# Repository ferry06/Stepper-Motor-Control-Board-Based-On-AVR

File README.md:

# Stepper-Motor-Control-Board-Based-On-AVR

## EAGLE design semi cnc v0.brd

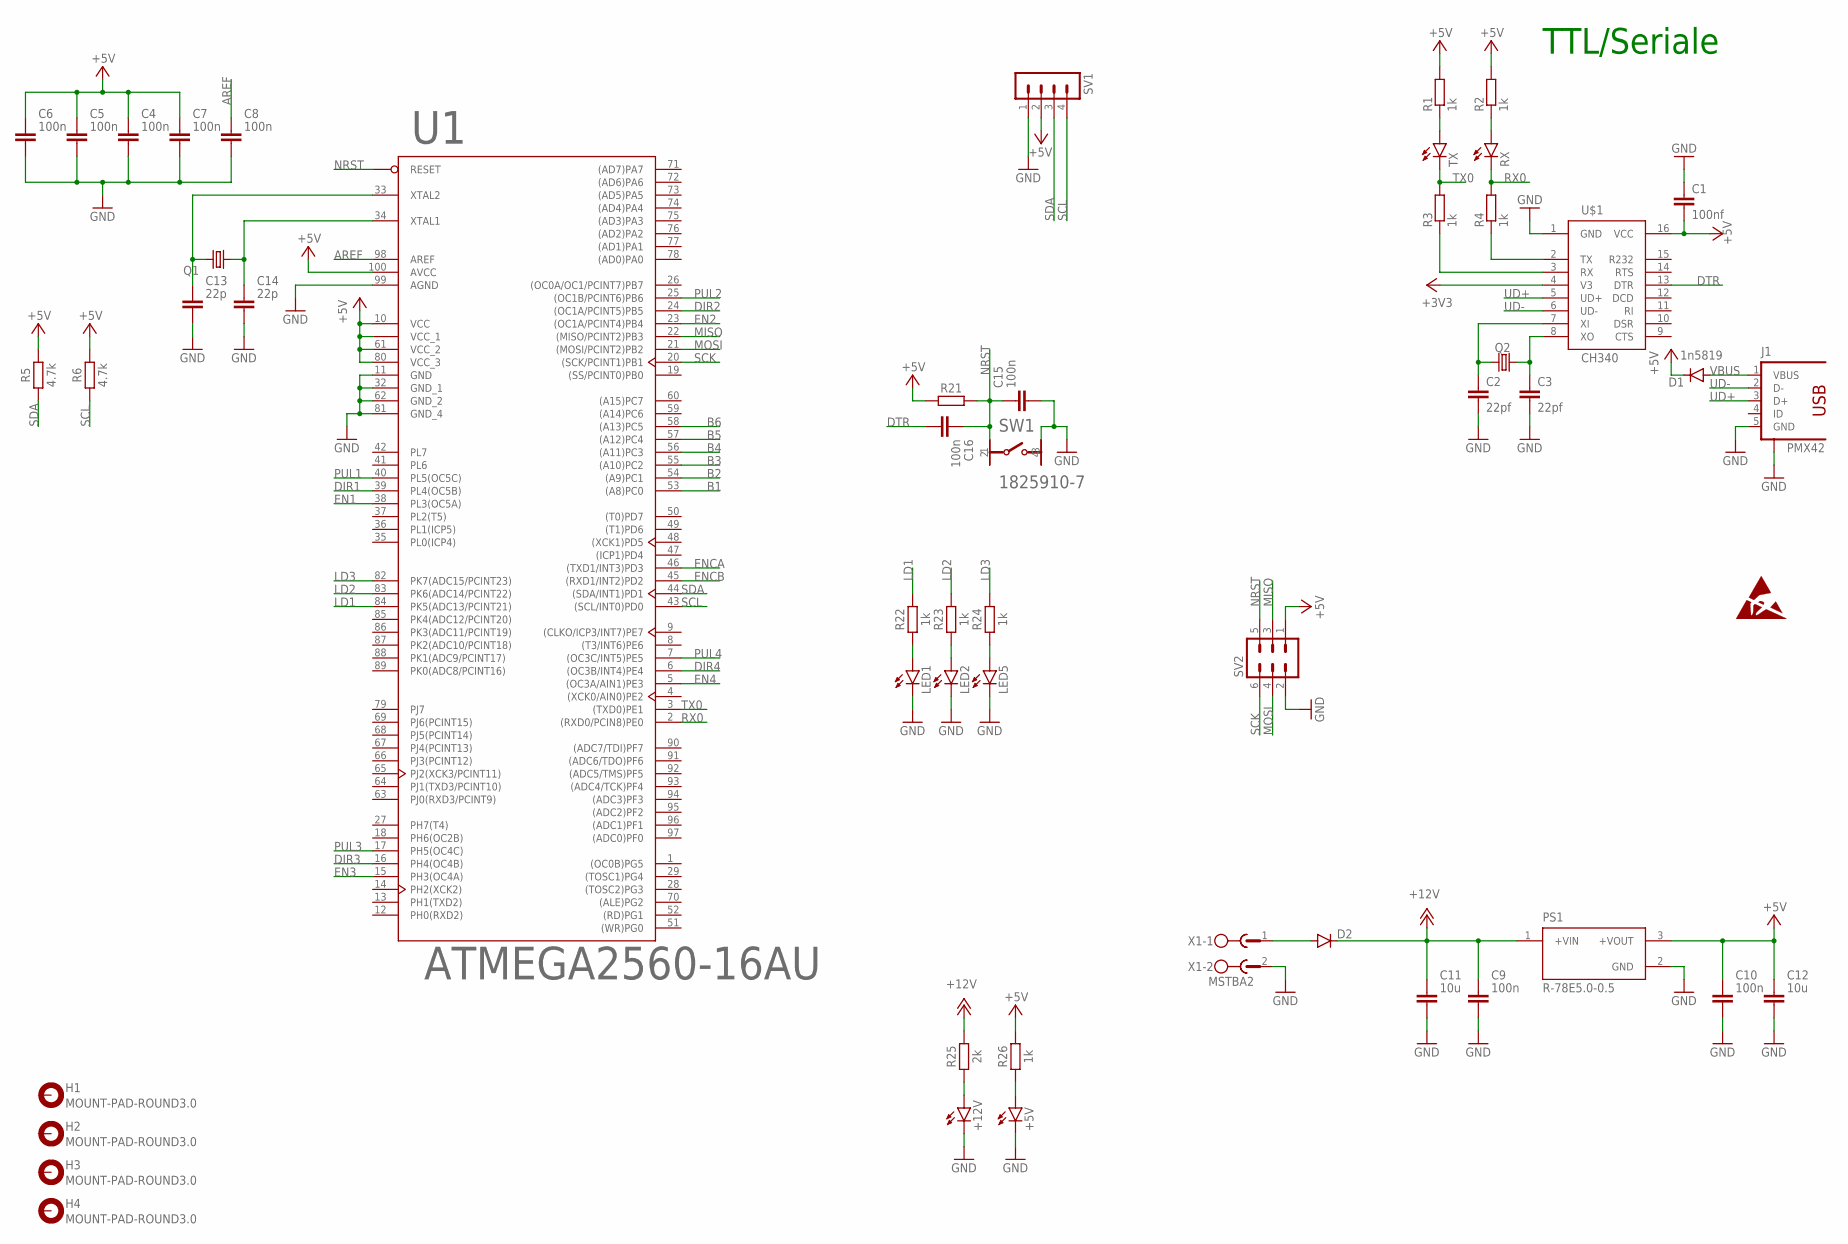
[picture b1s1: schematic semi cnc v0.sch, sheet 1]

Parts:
+5V, +12V: LEDCHIP-LED0805; CHIP-LED0805
C1: 100nf; C0805
C2, C3: 22pf; C0603
C4, C5, C6, C7, C8, C9, C10, C15, C16: 100n; CAPC1608X85
C11, C12: 10u; CAPC2012X110
C13, C14: 22p; CAPC1608X85
D1: 1n5819; SOD123
D2: DIODE-SOD123; SOD123
H1, H2, H3, H4: MOUNT-PAD-ROUND3.0; 3,0-PAD
J1: PMX42; PMX42_56579-0576
LED1, LED2, LED5: LEDCHIP-LED0805; CHIP-LED0805
PS1: R-78E5.0-0.5; CONV_R-78E5.0-0.5
Q1, Q2: KX-7; 3.2X2.5_KX-7
R1, R2, R3, R4: 1k; R0805
R5, R6: 4.7k; RESC1608X60
R21: R_CHIP-0603(1608-METRIC); RESC1608X60
R22, R23, R24, R26: 1k; RESC1608X60
R25: 2k; RESC1608X60
RX: LEDSML0805; SML0805
SV1: MA04-1
SV2: MA03-2
SW1: TE_1825910-7TE_1825910-7_0_0; TE_1825910-7_0
TX: LEDSML0805; SML0805
U1: ATMEGA2560-16AU; TQFP-100
U$1: CH340; SOIC16
X1: MSTBA2

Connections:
+3V3: U$1.4 (V3)
+5V: C1.2, C4.1, C5.1, C6.1, C7.1, C10.1, C12.1, D1.C, PS1.3 (+VOUT), R1.2, R2.2, R5.2, R6.2, R21.1, R26.2, SV1.2, SV2.1, U1.10 (VCC), U1.31 (VCC_1), U1.61 (VCC_2), U1.80 (VCC_3), U1.100 (AVCC), U$1.16 (VCC); also elsewhere on the board
+12V: C9.1, C11.1, D2.C, PS1.1 (+VIN), R25.2
AREF: C8.1, U1.98 (AREF)
B1: U1.53 ((A8)PC0); also elsewhere on the board
B2: U1.54 ((A9)PC1); also elsewhere on the board
B3: U1.55 ((A10)PC2); also elsewhere on the board
B4: U1.56 ((A11)PC3); also elsewhere on the board
B5: U1.57 ((A12)PC4); also elsewhere on the board
B6: U1.58 ((A13)PC5); also elsewhere on the board
DIR1: U1.39 (PL4(OC5B)); also elsewhere on the board
DIR2: U1.24 ((OC1A/PCINT5)PB5); also elsewhere on the board
DIR3: U1.16 (PH4(OC4B)); also elsewhere on the board
DIR4: U1.6 ((OC3B/INT4)PE4); also elsewhere on the board
DTR: C16.2, U$1.13 (DTR)
EN1: U1.38 (PL3(OC5A)); also elsewhere on the board
EN2: U1.23 ((OC1A/PCINT4)PB4); also elsewhere on the board
EN3: U1.15 (PH3(OC4A)); also elsewhere on the board
EN4: U1.5 ((OC3A/AIN1)PE3); also elsewhere on the board
ENCA: U1.46 ((TXD1/INT3)PD3); also elsewhere on the board
ENCB: U1.45 ((RXD1/INT2)PD2); also elsewhere on the board
GND: +5V.C, +12V.C, C1.1, C2.2, C3.2, C4.2, C5.2, C6.2, C7.2, C8.2, C9.2, C10.2, C11.2, C12.2, C13.2, C14.2, C15.2, J1.5 (GND), LED1.C, LED2.C, LED5.C, PS1.2 (GND), SV1.1, SV2.2, SW1.3, U1.11 (GND), U1.32 (GND_1), U1.62 (GND_2), U1.81 (GND_4), U1.99 (AGND), U$1.1 (GND), X1.2; also elsewhere on the board
LD1: R22.2, U1.84 (PK5(ADC13/PCINT21))
LD2: R23.2, U1.83 (PK6(ADC14/PCINT22))
LD3: R24.2, U1.82 (PK7(ADC15/PCINT23))
MISO: SV2.3, U1.22 ((MISO/PCINT2)PB3)
MOSI: SV2.4, U1.21 ((MOSI/PCINT2)PB2)
unnamed: J1.S1 (S), J1.S2 (S), J1.S3 (S), J1.S4 (S)
unnamed: D2.A, X1.1
unnamed: C13.1, Q1.3 (2), U1.33 (XTAL2)
unnamed: LED5.A, R24.1
unnamed: LED2.A, R23.1
unnamed: LED1.A, R22.1
unnamed: R4.1, U$1.2 (TX)
unnamed: R3.1, U$1.3 (RX)
unnamed: C3.1, Q2.1, U$1.8 (XO)
unnamed: C2.1, Q2.3 (2), U$1.7 (XI)
unnamed: R2.1, RX.A
unnamed: R1.1, TX.A
unnamed: C14.1, Q1.1, U1.34 (XTAL1)
unnamed: +12V.A, R25.1
unnamed: +5V.A, R26.1
NRST: C15.1, C16.1, R21.2, SV2.5, SW1.1, U1.30 (RESET)
PUL1: U1.40 (PL5(OC5C)); also elsewhere on the board
PUL2: U1.25 ((OC1B/PCINT6)PB6); also elsewhere on the board
PUL3: U1.17 (PH5(OC4C)); also elsewhere on the board
PUL4: U1.7 ((OC3C/INT5)PE5); also elsewhere on the board
RX0: R4.2, RX.C, U1.2 ((RXD0/PCIN8)PE0)
SCK: SV2.6, U1.20 ((SCK/PCINT1)PB1)
SCL: R6.1, SV1.4, U1.43 ((SCL/INT0)PD0)
SDA: R5.1, SV1.3, U1.44 ((SDA/INT1)PD1)
TX0: R3.2, TX.C, U1.3 ((TXD0)PE1)
UD+: J1.3 (D+), U$1.5 (UD+)
UD-: J1.2 (D-), U$1.6 (UD-)
VBUS: D1.A, J1.1 (VBUS)

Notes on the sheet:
TTL/Seriale

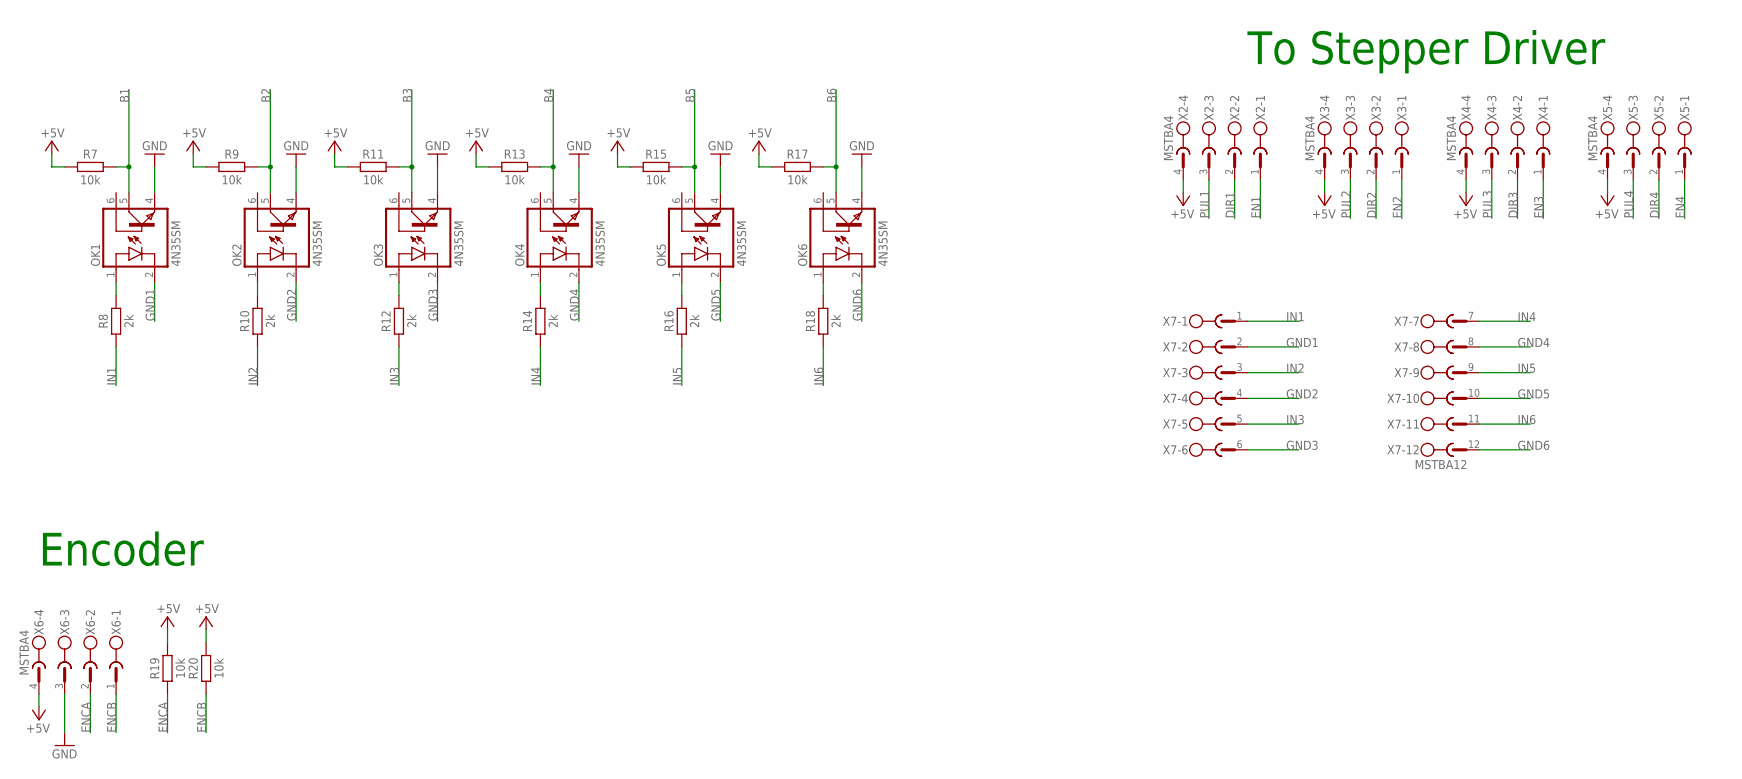
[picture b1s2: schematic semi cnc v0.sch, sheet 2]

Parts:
OK1, OK2, OK3, OK4, OK5, OK6: 4N35SM; DIL6-SMD
R7, R9, R11, R13, R15, R17, R19, R20: 10k; RESC1608X60
R8, R10, R12, R14, R16, R18: 2k; RESC1608X60
X2, X3, X4, X5, X6: MSTBA4
X7: MSTBA12

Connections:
+5V: R7.1, R9.1, R11.1, R13.1, R15.1, R17.1, R19.2, R20.2, X2.4, X3.4, X4.4, X5.4, X6.4; also elsewhere on the board
B1: OK1.5 (COL), R7.2; also elsewhere on the board
B2: OK2.5 (COL), R9.2; also elsewhere on the board
B3: OK3.5 (COL), R11.2; also elsewhere on the board
B4: OK4.5 (COL), R13.2; also elsewhere on the board
B5: OK5.5 (COL), R15.2; also elsewhere on the board
B6: OK6.5 (COL), R17.2; also elsewhere on the board
DIR1: X2.2; also elsewhere on the board
DIR2: X3.2; also elsewhere on the board
DIR3: X4.2; also elsewhere on the board
DIR4: X5.2; also elsewhere on the board
EN1: X2.1; also elsewhere on the board
EN2: X3.1; also elsewhere on the board
EN3: X4.1; also elsewhere on the board
EN4: X5.1; also elsewhere on the board
ENCA: R19.1, X6.2; also elsewhere on the board
ENCB: R20.1, X6.1; also elsewhere on the board
GND: OK1.4 (EMI), OK2.4 (EMI), OK3.4 (EMI), OK4.4 (EMI), OK5.4 (EMI), OK6.4 (EMI), X6.3; also elsewhere on the board
GND1: OK1.2 (C), X7.2
GND2: OK2.2 (C), X7.4
GND3: OK3.2 (C), X7.6
GND4: OK4.2 (C), X7.8
GND5: OK5.2 (C), X7.10
GND6: OK6.2 (C), X7.12
IN1: R8.1, X7.1
IN2: R10.1, X7.3
IN3: R12.1, X7.5
IN4: R14.1, X7.7
IN5: R16.1, X7.9
IN6: R18.1, X7.11
unnamed: OK4.1 (A), R14.2
unnamed: OK1.1 (A), R8.2
unnamed: OK5.1 (A), R16.2
unnamed: OK6.1 (A), R18.2
unnamed: OK2.1 (A), R10.2
unnamed: OK3.1 (A), R12.2
PUL1: X2.3; also elsewhere on the board
PUL2: X3.3; also elsewhere on the board
PUL3: X4.3; also elsewhere on the board
PUL4: X5.3; also elsewhere on the board

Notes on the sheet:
To Stepper Driver
Encoder

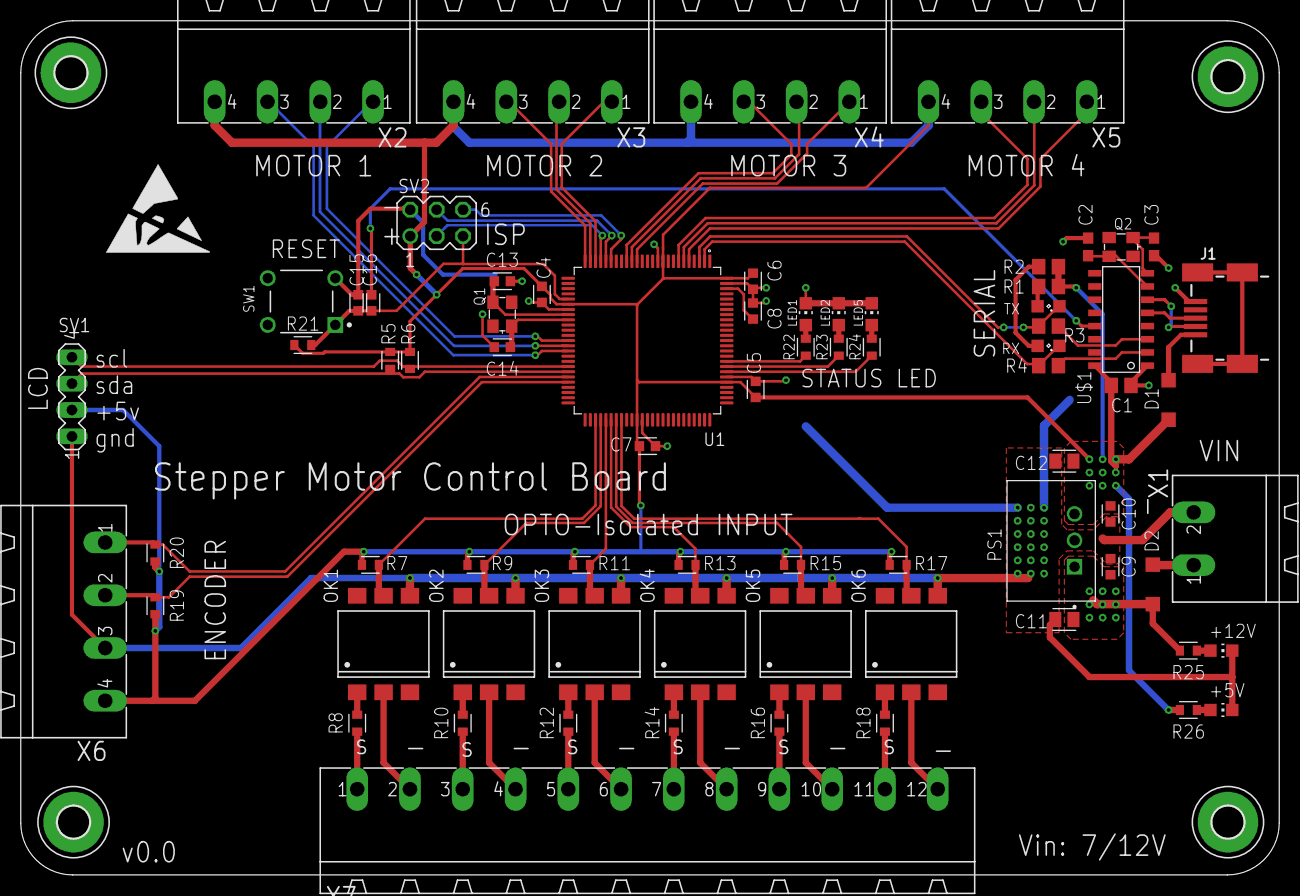
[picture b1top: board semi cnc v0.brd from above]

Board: 2 copper layers, 121.1 x 82.2 mm, 78 parts (0 on the bottom side), 72 nets.

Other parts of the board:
U$2: ESD_10.00

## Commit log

2020-11-07 Create Read Me

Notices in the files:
parts and their libraries:
crystal-geyer_V1_0: Copyright: Geyer-Electronic
